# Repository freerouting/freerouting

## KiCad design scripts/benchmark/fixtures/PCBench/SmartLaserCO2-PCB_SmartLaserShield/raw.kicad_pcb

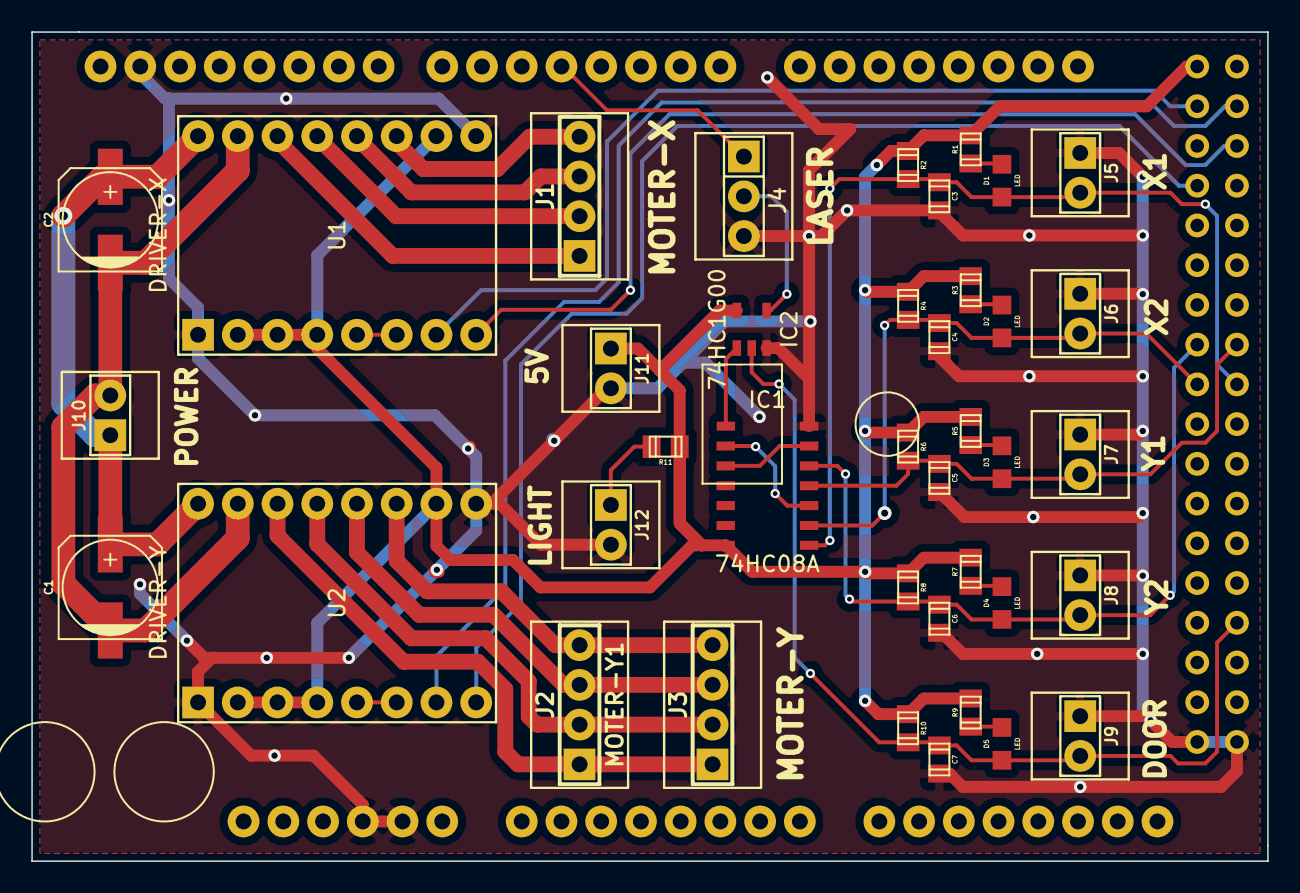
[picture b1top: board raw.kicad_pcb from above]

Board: 2 copper layers, 79.0 x 53.0 mm, 40 parts (0 on the bottom side), 34 nets.

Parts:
C1, C2: 100uF; C_ELEC_6.3x7.7
C3, C4, C5, C6, C7: 0u1; C_0805
D1, D2, D3, D4, D5: LED; C_LED
IC1: 74HC08A
IC2: 74HC1G00
J1: MOTER-X; PIN_ARRAY_4x1
J2: MOTER-Y1; PIN_ARRAY_4x1
J3: MOTER-Y; PIN_ARRAY_4x1
J4: LASER; PIN_ARRAY_3X1
J5: X1; PIN_ARRAY_2X1
J6: X2; PIN_ARRAY_2X1
J7: Y1; PIN_ARRAY_2X1
J8: Y2; PIN_ARRAY_2X1
J9: DOOR; PIN_ARRAY_2X1
J10: POWER; PIN_ARRAY_2X1
J11: 5V; PIN_ARRAY_2X1
J12: LIGHT; PIN_ARRAY_2X1
R1, R3, R5, R7, R9: 1K; C_0805
R2, R4, R6, R8, R10: 10K; C_0805
R11: 150; C_0805
U1: DRIVER-X; A4988
U2: DRIVER-Y; A4988
U3: ARDUINO_MEGA

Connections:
GND: C3.1, C4.1, C5.1, C6.1, C7.1, IC1.7, IC2.3, J4.3, J5.1, J6.1, J7.1, J8.1, J9.1, J11.2, J12.2, U1.1, U1.9, U2.1, U2.9, U3.GND1, U3.GND2, U3.GND3, U3.GND4, U3.GND5
unnamed: J1.2, U1.13
unnamed: J1.3, U1.12
unnamed: J1.4, U1.11
unnamed: J1.1, U1.14
unnamed: IC1.8, IC2.1
unnamed: J2.3, J3.3, U2.12
unnamed: J2.1, J3.1, U2.14
unnamed: J2.2, J3.2, U2.13
unnamed: J2.4, J3.4, U2.11
unnamed: U1.5, U1.6
unnamed: U2.5, U2.6
unnamed: IC1.3, IC1.9
unnamed: IC1.6, IC1.10
unnamed: J4.1, U3.4
unnamed: U1.7, U3.22
unnamed: U2.7, U3.23
unnamed: IC2.4, J4.2
unnamed: J12.1, R11.1
unnamed: U1.8, U3.25
unnamed: U2.8, U3.26
unnamed: D3.1, R5.2
unnamed: D1.1, R1.2
unnamed: C3.2, D1.2, IC1.1, J5.2, R2.1, U3.37
unnamed: D2.1, R3.2
unnamed: C4.2, D2.2, IC1.2, J6.2, R4.1, U3.36
unnamed: C6.2, D4.2, IC1.5, J8.2, R8.1, U3.34
unnamed: D5.1, R9.2
unnamed: C7.2, D5.2, IC2.2, J9.2, R10.1, U3.49
unnamed: C5.2, D3.2, IC1.4, J7.2, R6.1, U3.35
unnamed: D4.1, R7.2
unnamed: C1.1, C2.1, J10.1, U1.16, U2.16
unnamed: C1.2, C2.2, J10.2, U1.15, U2.15
VDD: IC1.14, IC2.5, J11.1, R1.1, R2.2, R3.1, R4.2, R5.1, R6.2, R7.1, R8.2, R9.1, R10.2, R11.2, U1.2, U1.3, U1.4, U1.10, U2.2, U2.3, U2.4, U2.10, U3.5V_4

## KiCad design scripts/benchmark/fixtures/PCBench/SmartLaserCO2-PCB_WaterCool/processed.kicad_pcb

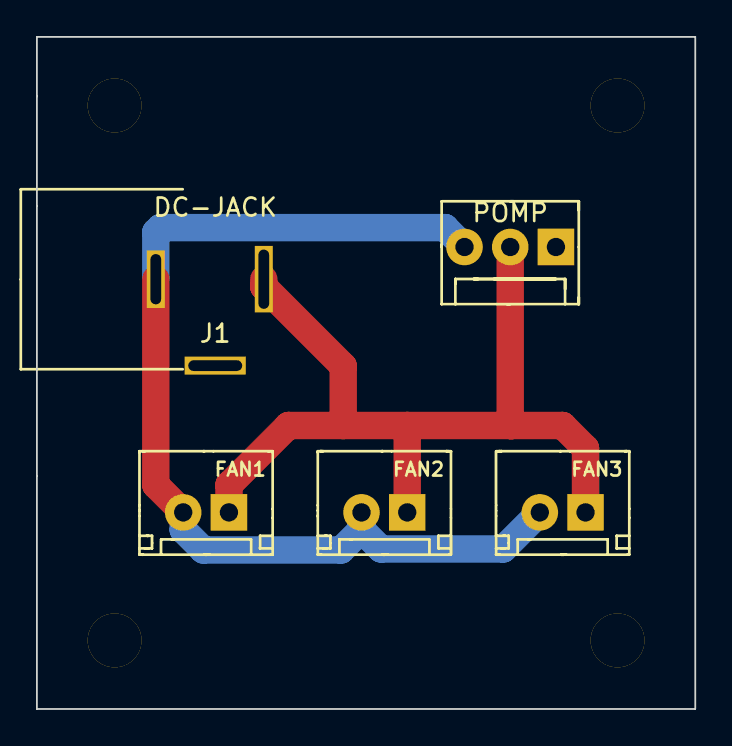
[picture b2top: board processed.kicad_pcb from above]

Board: 2 copper layers, 36.6 x 37.3 mm, 9 parts (0 on the bottom side), 2 nets.

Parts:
J1: DC-JACK; DC-005
J2: POMP; 640454-3
J3: FAN1; B2B-XH-A
J4: FAN2; B2B-XH-A
J5: FAN3; B2B-XH-A
Ref**: Val**; HOLE_M3
Ref**_2, Ref**_3, Ref**_4: Val**; HOLE_M3

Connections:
+12V: J1.1, J2.2, J3.1, J4.1, J5.1
GND: J1.2, J2.3, J3.2, J4.2, J5.2
